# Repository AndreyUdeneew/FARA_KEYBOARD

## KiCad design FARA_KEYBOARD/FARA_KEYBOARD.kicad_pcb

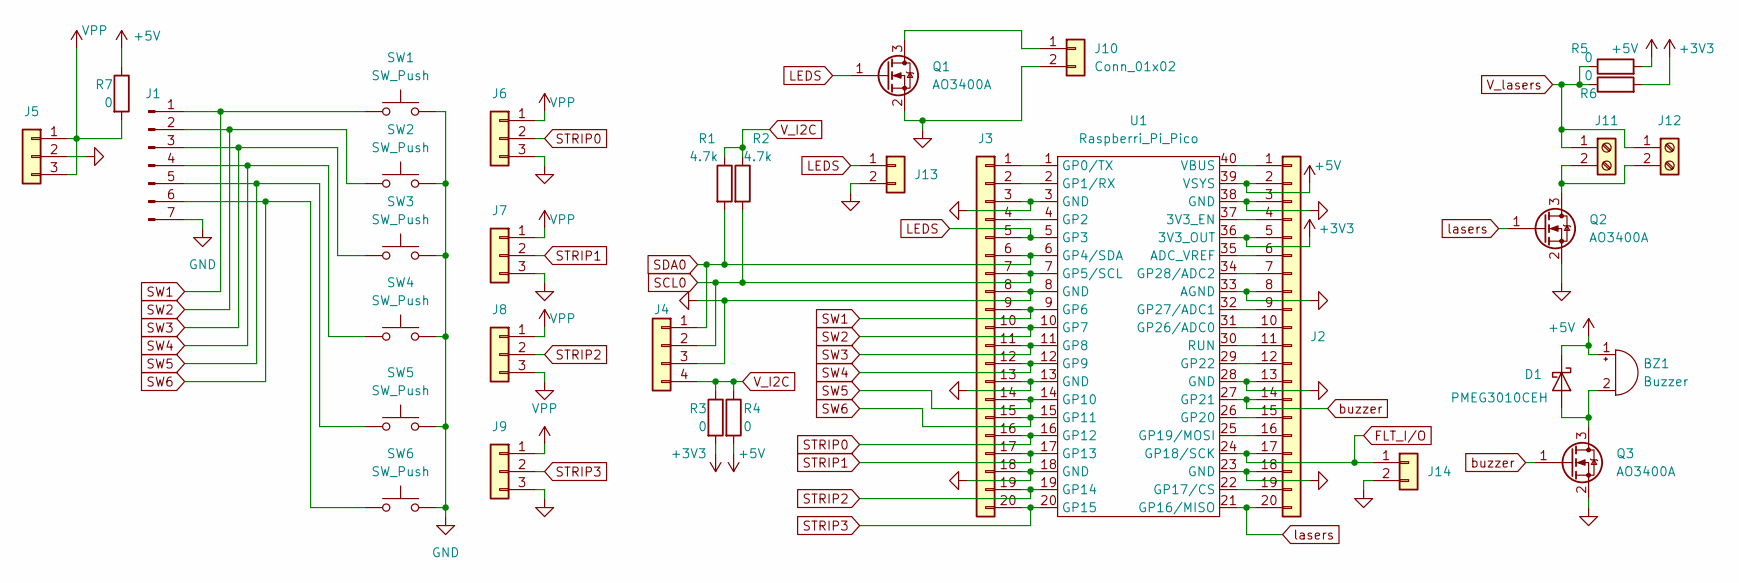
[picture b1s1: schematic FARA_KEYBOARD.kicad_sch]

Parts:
BZ1: Buzzer; PinHeader_1x02_P2.54mm_Vertical
D1: PMEG3010CEH; D_SOD-123F
J1: Conn_01x07_Pin; PinHeader_1x07_P2.54mm_Vertical
J2, J3: Conn_01x20; PinSocket_1x20_P2.54mm_Vertical
J4: Conn_01x04; PinSocket_1x04_P2.54mm_Vertical
J5, J6, J7, J8, J9: Conn_01x03; PinSocket_1x03_P2.54mm_Vertical
J10, J13, J14: Conn_01x02; PinSocket_1x02_P2.54mm_Vertical
J11, J12: Screw_Terminal_01x02; PinSocket_1x02_P2.54mm_Vertical
Q1, Q2, Q3: AO3400A; SOT-23
R1, R2: 4.7k; R_0603_1608Metric_Pad0.98x0.95mm_HandSolder
R3, R4, R5, R6: 0; R_0402_1005Metric_Pad0.72x0.64mm_HandSolder
R7: 0; R_0805_2012Metric_Pad1.20x1.40mm_HandSolder
SW1, SW2, SW3, SW4, SW5, SW6: SW_Push; SW_PUSH_6mm
U1: Raspberri_Pi_Pico; Raspberry Pi Pico

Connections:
+3V3: J2.5, R3.2, R6.2, U1.36 (3V3_OUT)
+5V: BZ1.1 (-), D1.1 (K), J2.2, R4.2, R5.2, R7.1, U1.39 (VSYS)
FLT_I/O: J2.17, J14.1, U1.24 (GP18/SCK)
GND: J1.7, J2.3, J2.8, J2.13, J2.18, J3.3, J3.8, J3.13, J3.18, J4.3, J5.2, J6.3, J7.3, J8.3, J9.3, J10.2, J13.2, J14.2, Q1.2 (S), Q2.2 (S), Q3.2 (S), SW1.2, SW2.2, SW3.2, SW4.2, SW5.2, SW6.2, U1.3 (GND), U1.8 (GND), U1.13 (GND), U1.18 (GND), U1.23 (GND), U1.28 (GND), U1.33 (AGND), U1.38 (GND)
LEDS: J3.5, J13.1, Q1.1 (G), U1.5 (GP3)
unnamed: BZ1.2 (+), D1.2 (A), Q3.3 (D)
unnamed: J2.1, U1.40 (VBUS)
unnamed: J2.4, U1.37 (3V3_EN)
unnamed: J2.6, U1.35 (ADC_VREF)
unnamed: J2.7, U1.34 (GP28/ADC2)
unnamed: J2.9, U1.32 (GP27/ADC1)
unnamed: J2.10, U1.31 (GP26/ADC0)
unnamed: J2.11, U1.30 (RUN)
unnamed: J2.12, U1.29 (GP22)
unnamed: J2.15, U1.26 (GP20)
unnamed: J2.16, U1.25 (GP19/MOSI)
unnamed: J2.19, U1.22 (GP17/CS)
unnamed: J3.1, U1.1 (GP0/TX)
unnamed: J3.2, U1.2 (GP1/RX)
unnamed: J3.4, U1.4 (GP2)
unnamed: J10.1, Q1.3 (D)
unnamed: J11.2, J12.2, Q2.3 (D)
SCL0: J3.7, J4.2, R2.2, U1.7 (GP5/SCL)
SDA0: J3.6, J4.1, R1.2, U1.6 (GP4/SDA)
STRIP0: J3.16, J6.2, U1.16 (GP12)
STRIP1: J3.17, J7.2, U1.17 (GP13)
STRIP2: J3.19, J8.2, U1.19 (GP14)
STRIP3: J3.20, J9.2, U1.20 (GP15)
SW1: J1.1, J3.9, SW1.1, U1.9 (GP6)
SW2: J1.2, J3.10, SW2.1, U1.10 (GP7)
SW3: J1.3, J3.11, SW3.1, U1.11 (GP8)
SW4: J1.4, J3.12, SW4.1, U1.12 (GP9)
SW5: J1.5, J3.14, SW5.1, U1.14 (GP10)
SW6: J1.6, J3.15, SW6.1, U1.15 (GP11)
VPP: J5.1, J5.3, J6.1, J7.1, J8.1, J9.1, R7.2
V_I2C: J4.4, R1.1, R2.1, R3.1, R4.1
V_lasers: J11.1, J12.1, R5.1, R6.1
buzzer: J2.14, Q3.1 (G), U1.27 (GP21)
lasers: J2.20, Q2.1 (G), U1.21 (GP16/MISO)

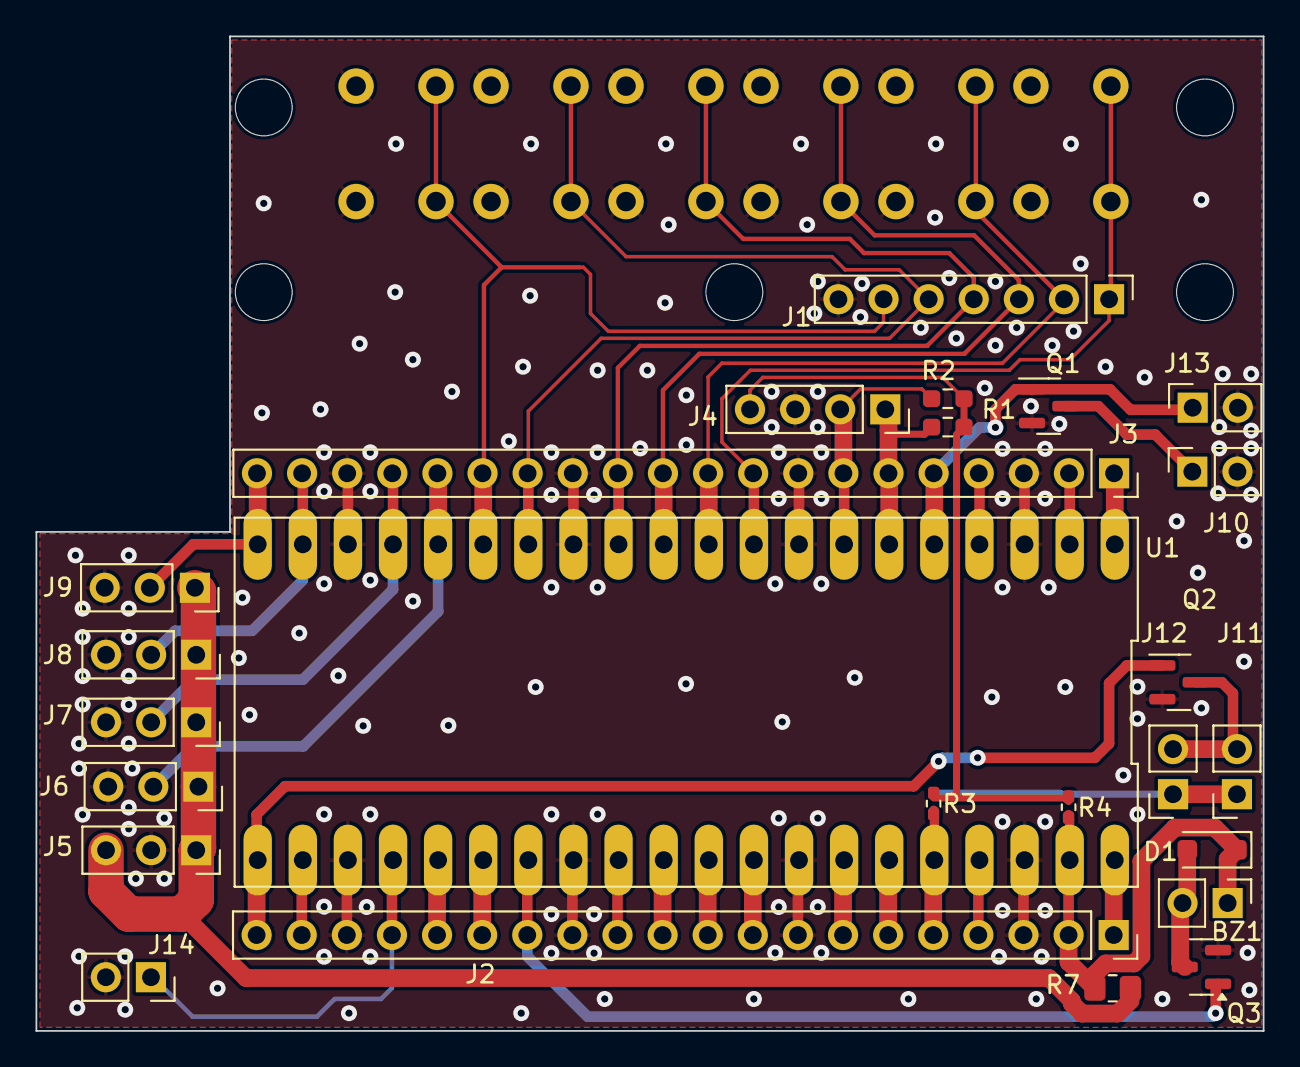
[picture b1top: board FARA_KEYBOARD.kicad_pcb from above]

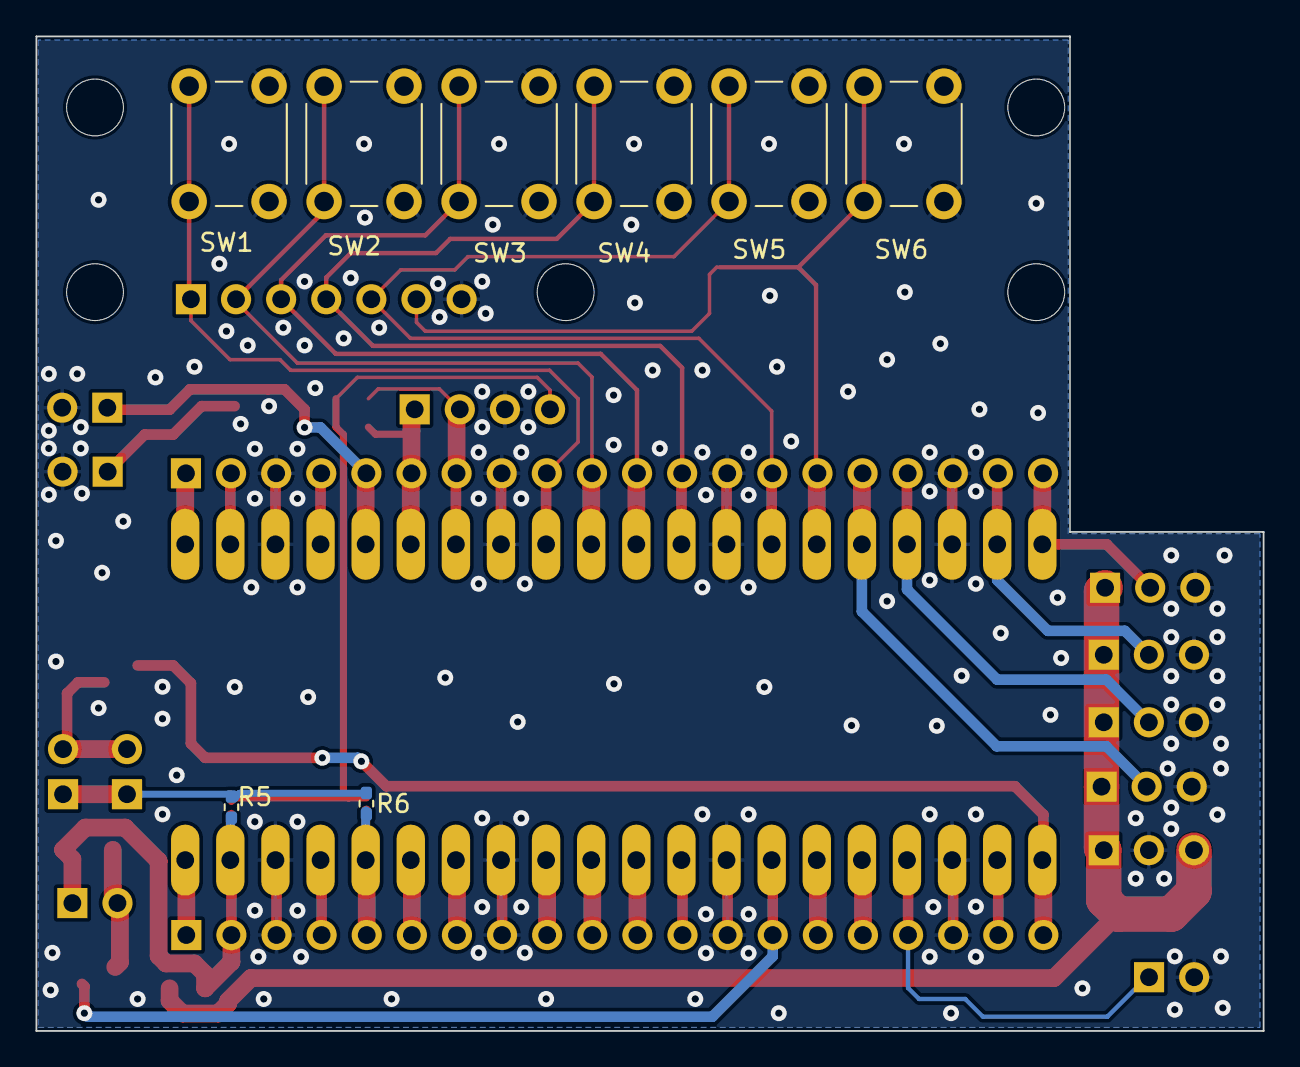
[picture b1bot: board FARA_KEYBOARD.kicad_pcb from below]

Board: 2 copper layers, 69.1 x 56.0 mm, 33 parts (8 on the bottom side), 39 nets.

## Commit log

2024-04-05 v0.1 Seems 2B ready
2024-04-05 v0.2 Gerbers were created, DR was conducted
2024-05-12 v0.3 Circuit was completed
2024-05-22 v0.4 circuit is ready
2024-05-22 v0.5 draft PCB was routed
2024-05-24 v0.6 seems 2B ready
2024-06-06 v0.7 form was corrected
2024-06-07 v0.8 reverted, ordered advanced.
